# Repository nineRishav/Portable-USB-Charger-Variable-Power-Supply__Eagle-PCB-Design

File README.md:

# Portable USB Charger & Variable Power Supply: Eagle-PCB-Design

### Variable Power Supply

---

### Portable USB Charger

[Link of Resource](https://www.build-electronic-circuits.com/portable-usb-charger-circuit/)

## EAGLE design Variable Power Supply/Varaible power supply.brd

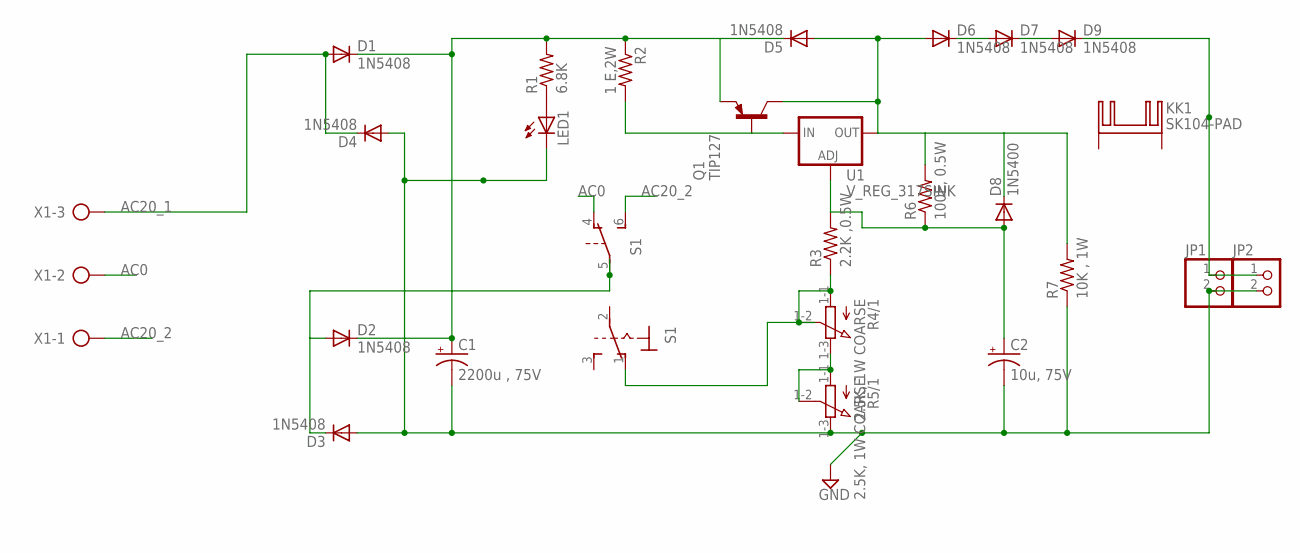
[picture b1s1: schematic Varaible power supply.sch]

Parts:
C1: 2200u , 75V; E5-13
C2: 10u, 75V; E5-13
D1, D2, D3, D4, D5, D6, D7, D9: 1N5408; DO201-15
D8: 1N5400; DO201-15
JP1, JP2: PINHD-1X2; 1X02
KK1: SK104-PAD
LED1: LED5MM
Q1: TIP127; TO220
R1: 6.8K; 0411/15
R2: 1 E,2W; 0411/15
R3: 2.2K ,0.5W; 0411/15
R4, R5: 2.5K, 1W COARSE; 3RP/1610G
R6: 100E, 0.5W; 0411/15
R7: 10K , 1W; 0411/15
S1: 320-938
U1: V_REG_317SINK; TO220-ADJ
X1: AK500/3-H

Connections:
AC0: S1.4 (O), X1.2
AC20_1: D1.A, D4.C, X1.3
AC20_2: S1.6 (S), X1.1
GND: C1.-, C2.-, D3.A, D4.A, JP1.2, JP2.2, LED1.K (C), R5.1-3 (E), R7.1
unnamed: D6.C, D7.A
unnamed: D7.C, D9.A
unnamed: C1.+, D1.C, D2.C, D5.C, Q1.3 (E), R1.2, R2.1
unnamed: LED1.A, R1.1
unnamed: Q1.1 (B), R2.2, U1.IN
unnamed: D5.A, D6.A, D8.C, Q1.2 (C), R6.2, R7.2, U1.OUT
unnamed: C2.+, D8.A, R3.2, R6.1, U1.ADJ
unnamed: R3.1, R4.1-1 (A), R4.1-2 (S), S1.1 (O)
unnamed: R4.1-3 (E), R5.1-1 (A), R5.1-2 (S)
unnamed: D9.C, JP1.1, JP2.1
unnamed: D2.A, D3.C, S1.5

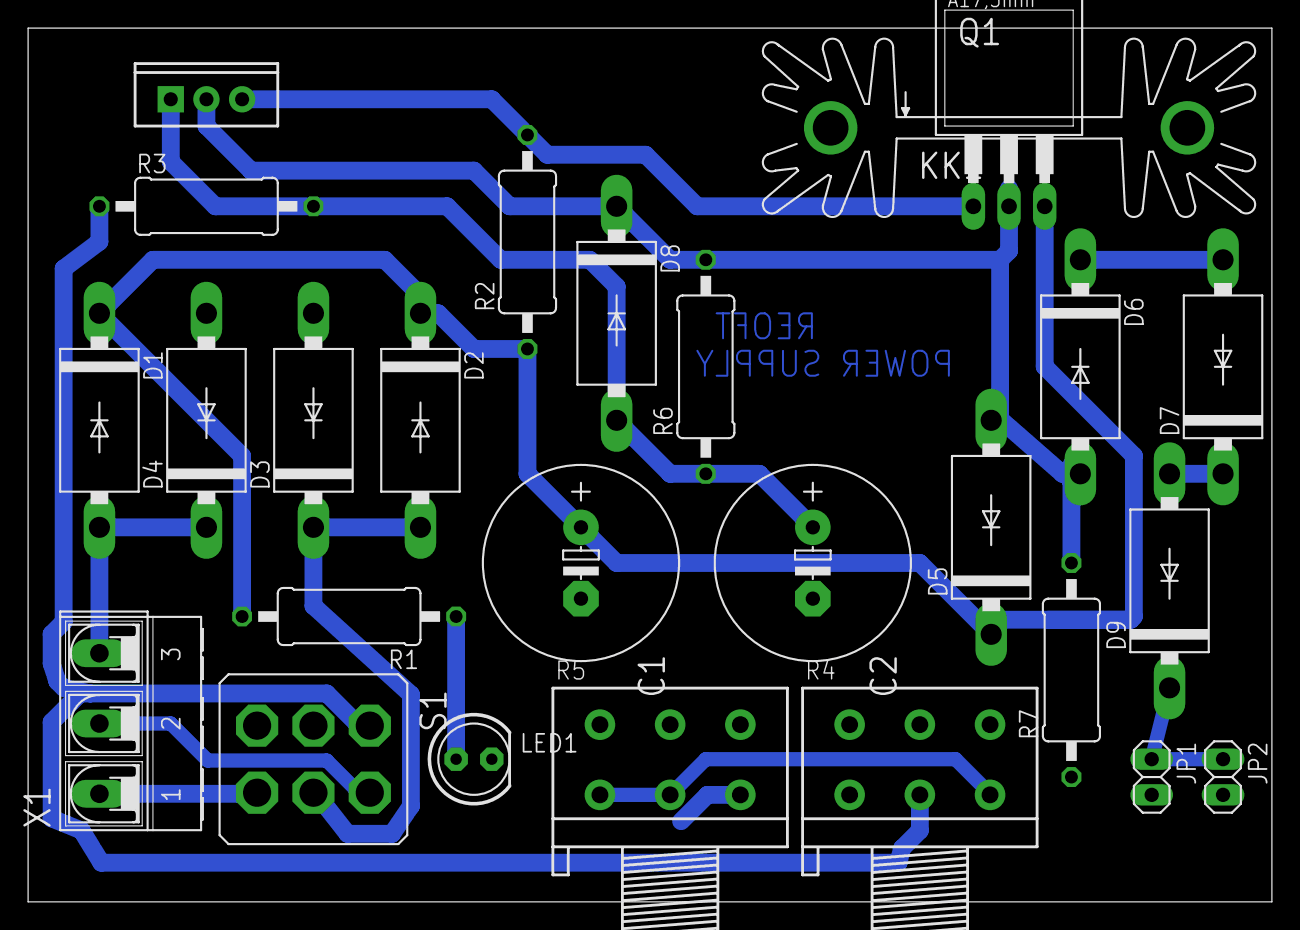
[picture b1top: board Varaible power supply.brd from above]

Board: 2 copper layers, 88.6 x 62.2 mm, 26 parts (0 on the bottom side), 15 nets.

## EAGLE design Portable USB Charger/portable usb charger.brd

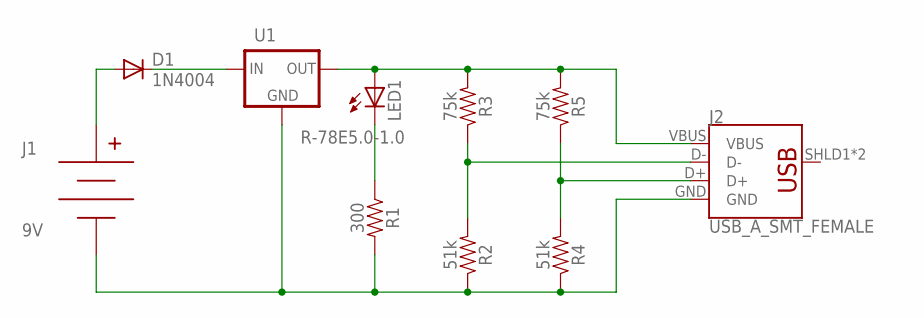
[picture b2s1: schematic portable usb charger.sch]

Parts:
D1: 1N4004; DO41-10
J1: 9V; BC9VPC
J2: USB_A_SMT_FEMALE; USB-A-S-SILK-FEMALE
LED1: LED3MM
R1: 300; 0603
R2, R4: 51k; 0603
R3, R5: 75k; 0603
U1: R-78E5.0-1.0; DC-DC_CONVERTER_78XX

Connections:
unnamed: D1.A, J1.V+
unnamed: D1.C, U1.VIN (IN)
unnamed: J2.VBUS, LED1.A, R3.2, R5.2, U1.VOUT (OUT)
unnamed: LED1.K (C), R1.1
unnamed: J1.V-, J2.GND, R1.2, R2.1, R4.1, U1.GND
unnamed: J2.D-, R2.2, R3.1
unnamed: J2.D+, R4.2, R5.1

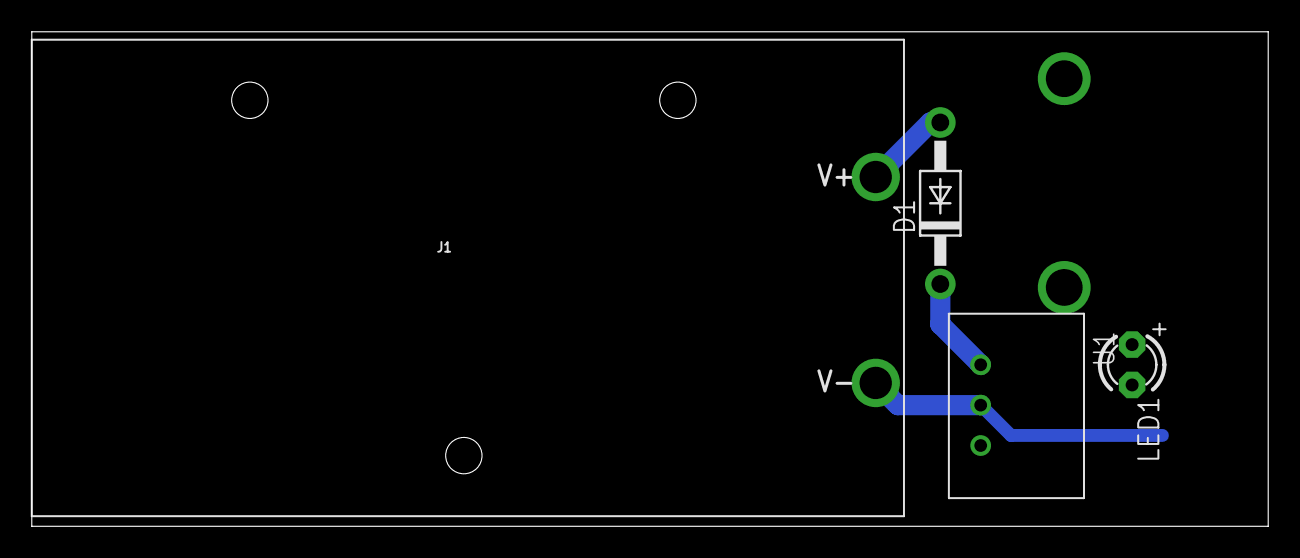
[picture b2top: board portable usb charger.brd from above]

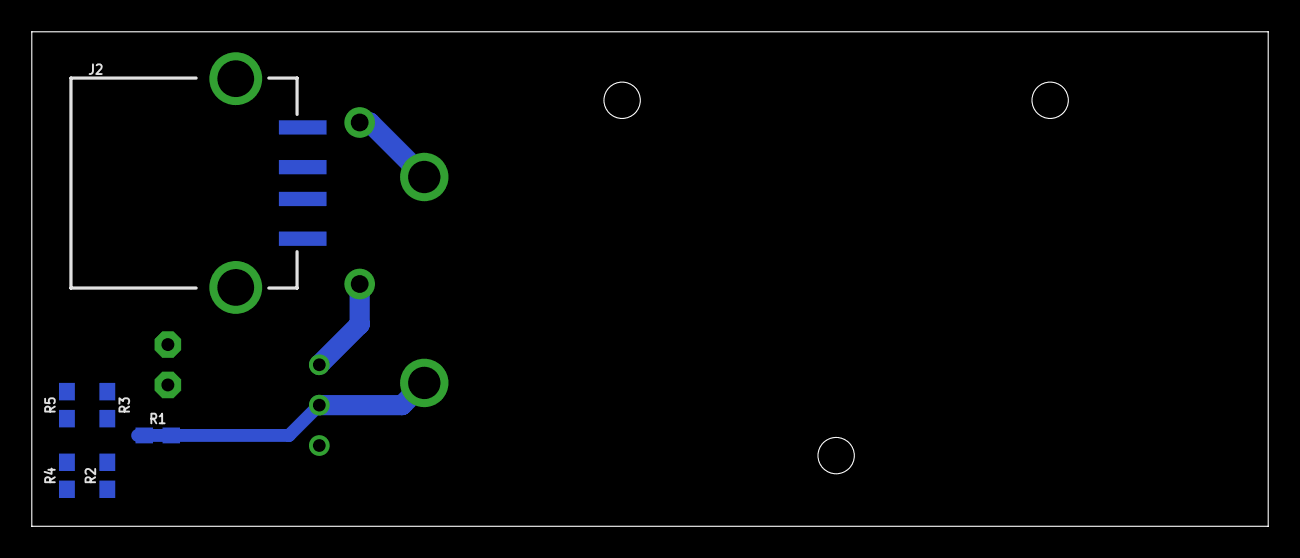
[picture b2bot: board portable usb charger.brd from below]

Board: 2 copper layers, 77.8 x 31.1 mm, 10 parts (6 on the bottom side), 7 nets.

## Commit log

2019-09-08 USB Charger - IoT Internship
2019-09-08 Variable Power Supply - Eagle Files - Internship
2019-09-17 Diagram
2019-09-17 README | PCB Board | eagle

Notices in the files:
parts and their libraries:
SparkFun-Connectors: Licensing: Creative Commons ShareAlike 4.0 International - https://creativecommons.org/licenses/by-sa/4.0
